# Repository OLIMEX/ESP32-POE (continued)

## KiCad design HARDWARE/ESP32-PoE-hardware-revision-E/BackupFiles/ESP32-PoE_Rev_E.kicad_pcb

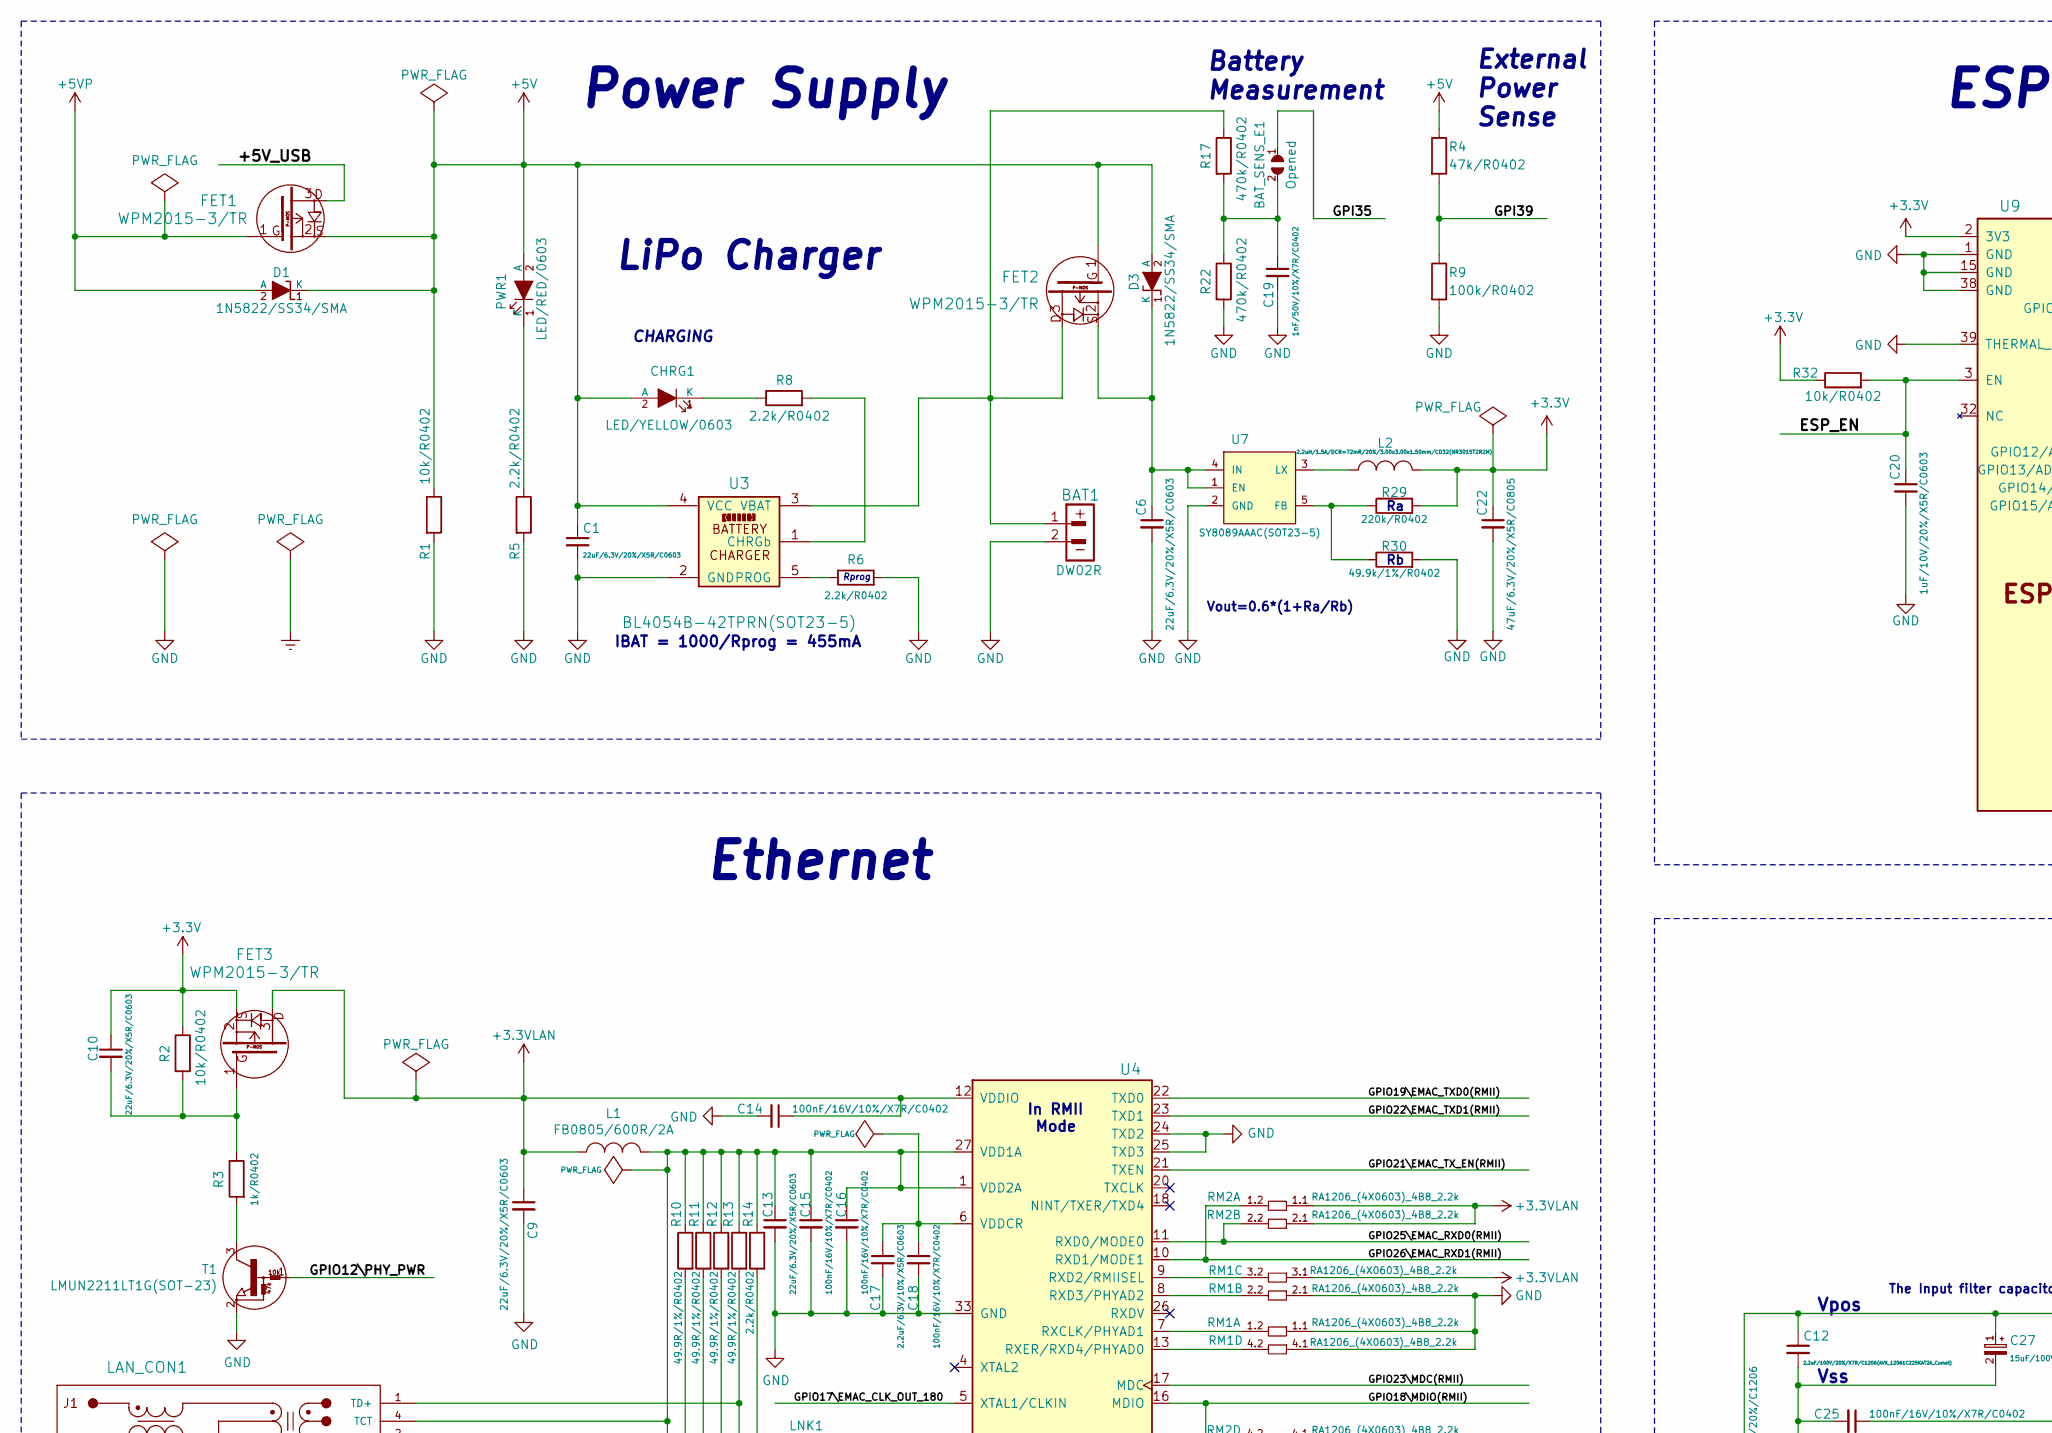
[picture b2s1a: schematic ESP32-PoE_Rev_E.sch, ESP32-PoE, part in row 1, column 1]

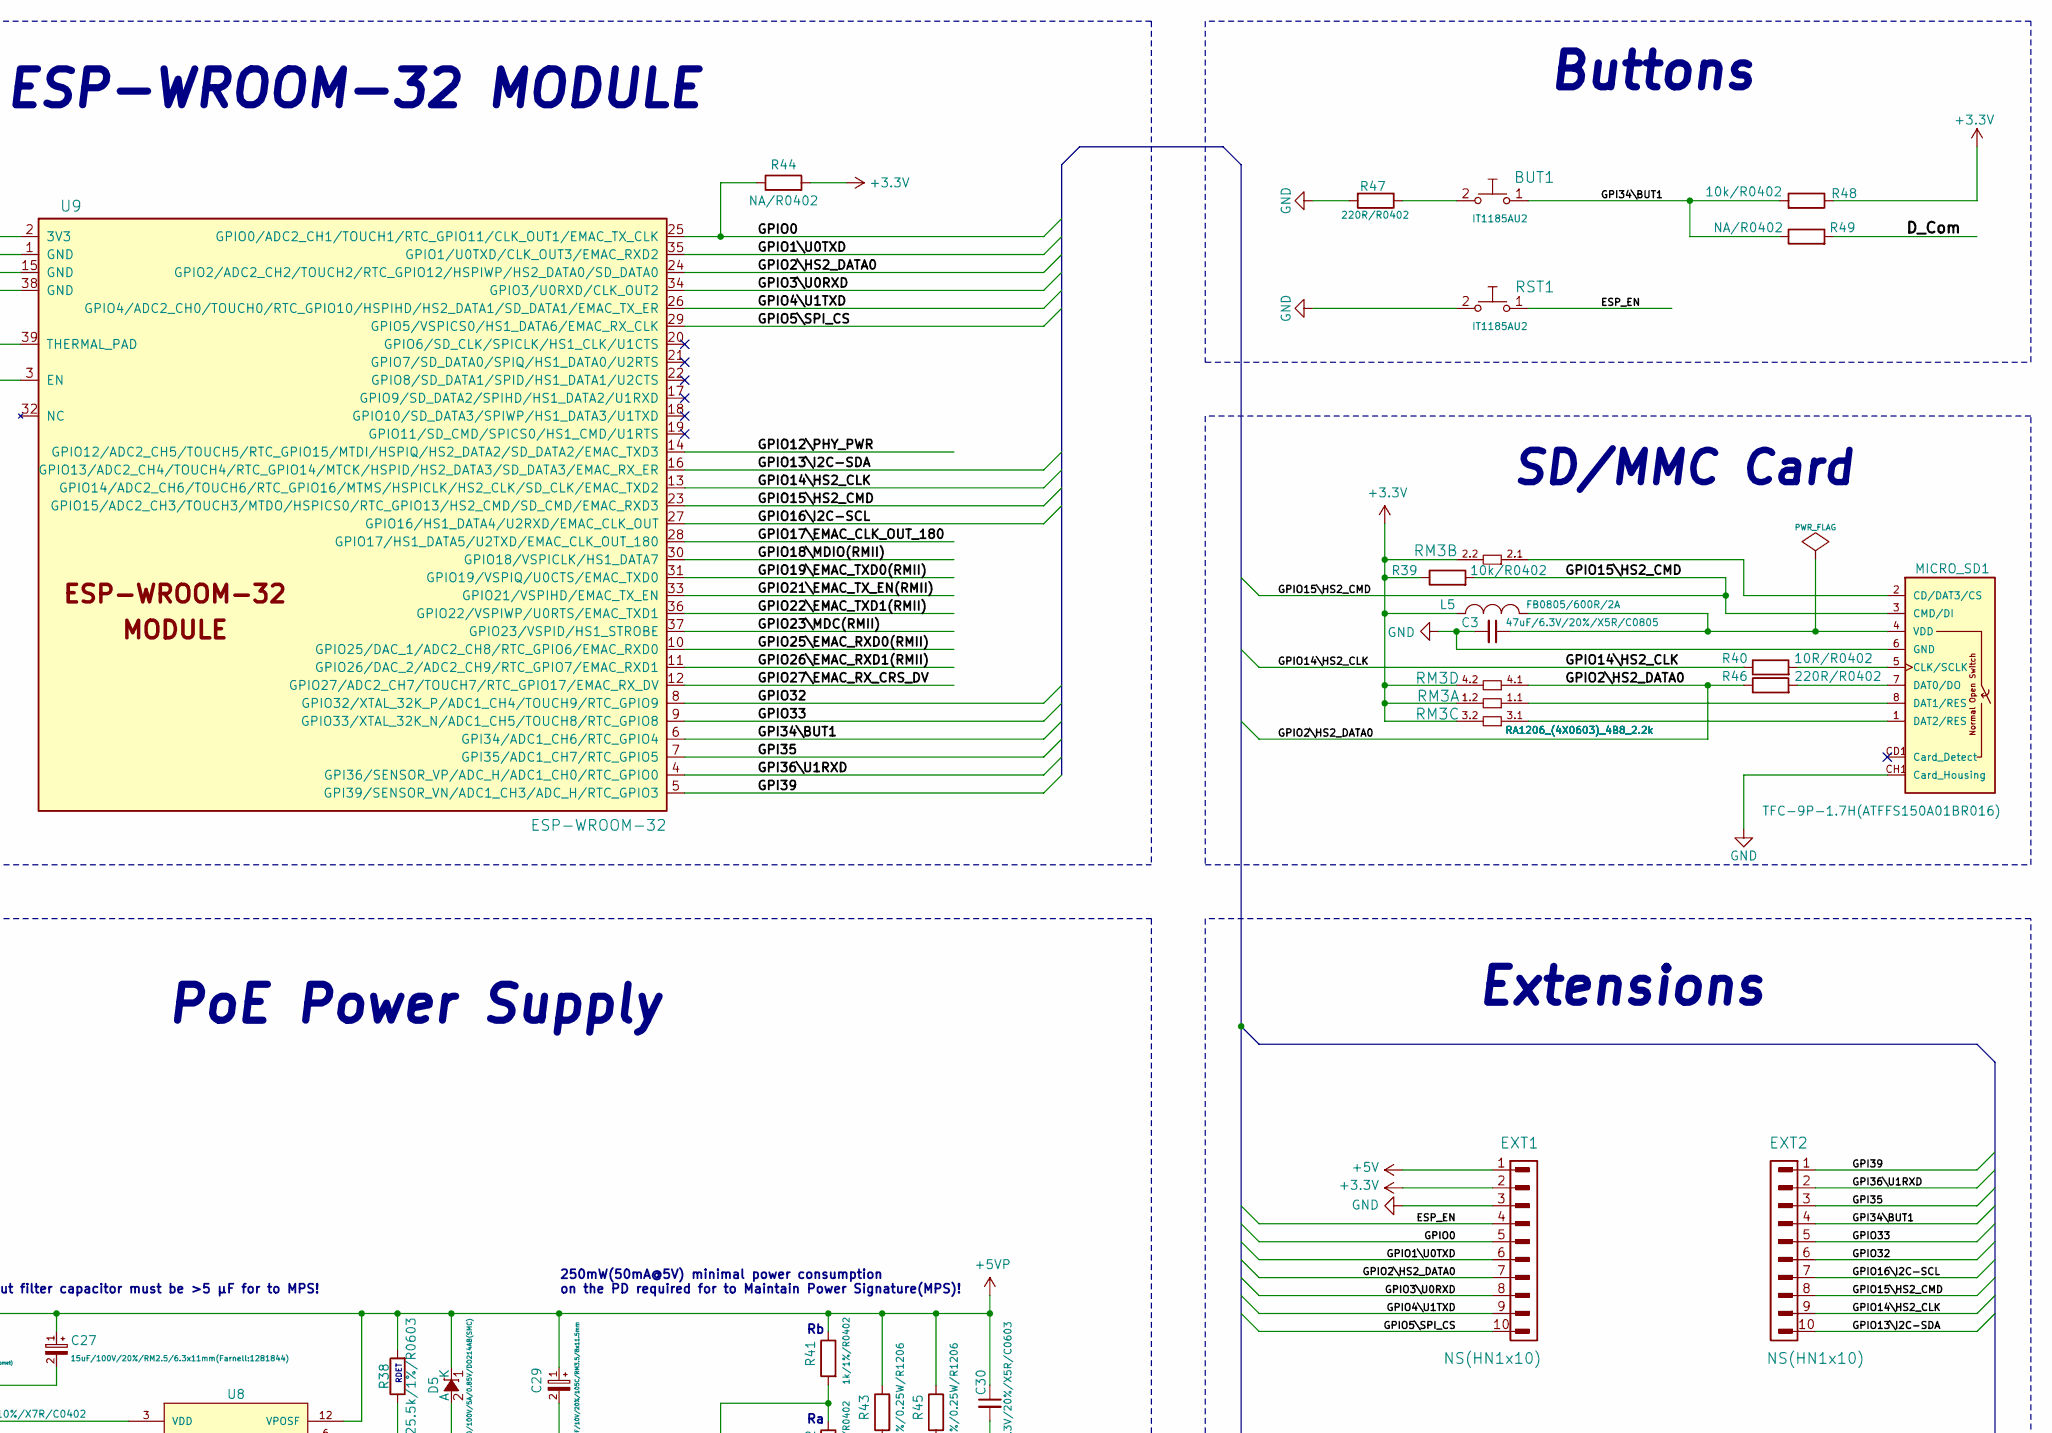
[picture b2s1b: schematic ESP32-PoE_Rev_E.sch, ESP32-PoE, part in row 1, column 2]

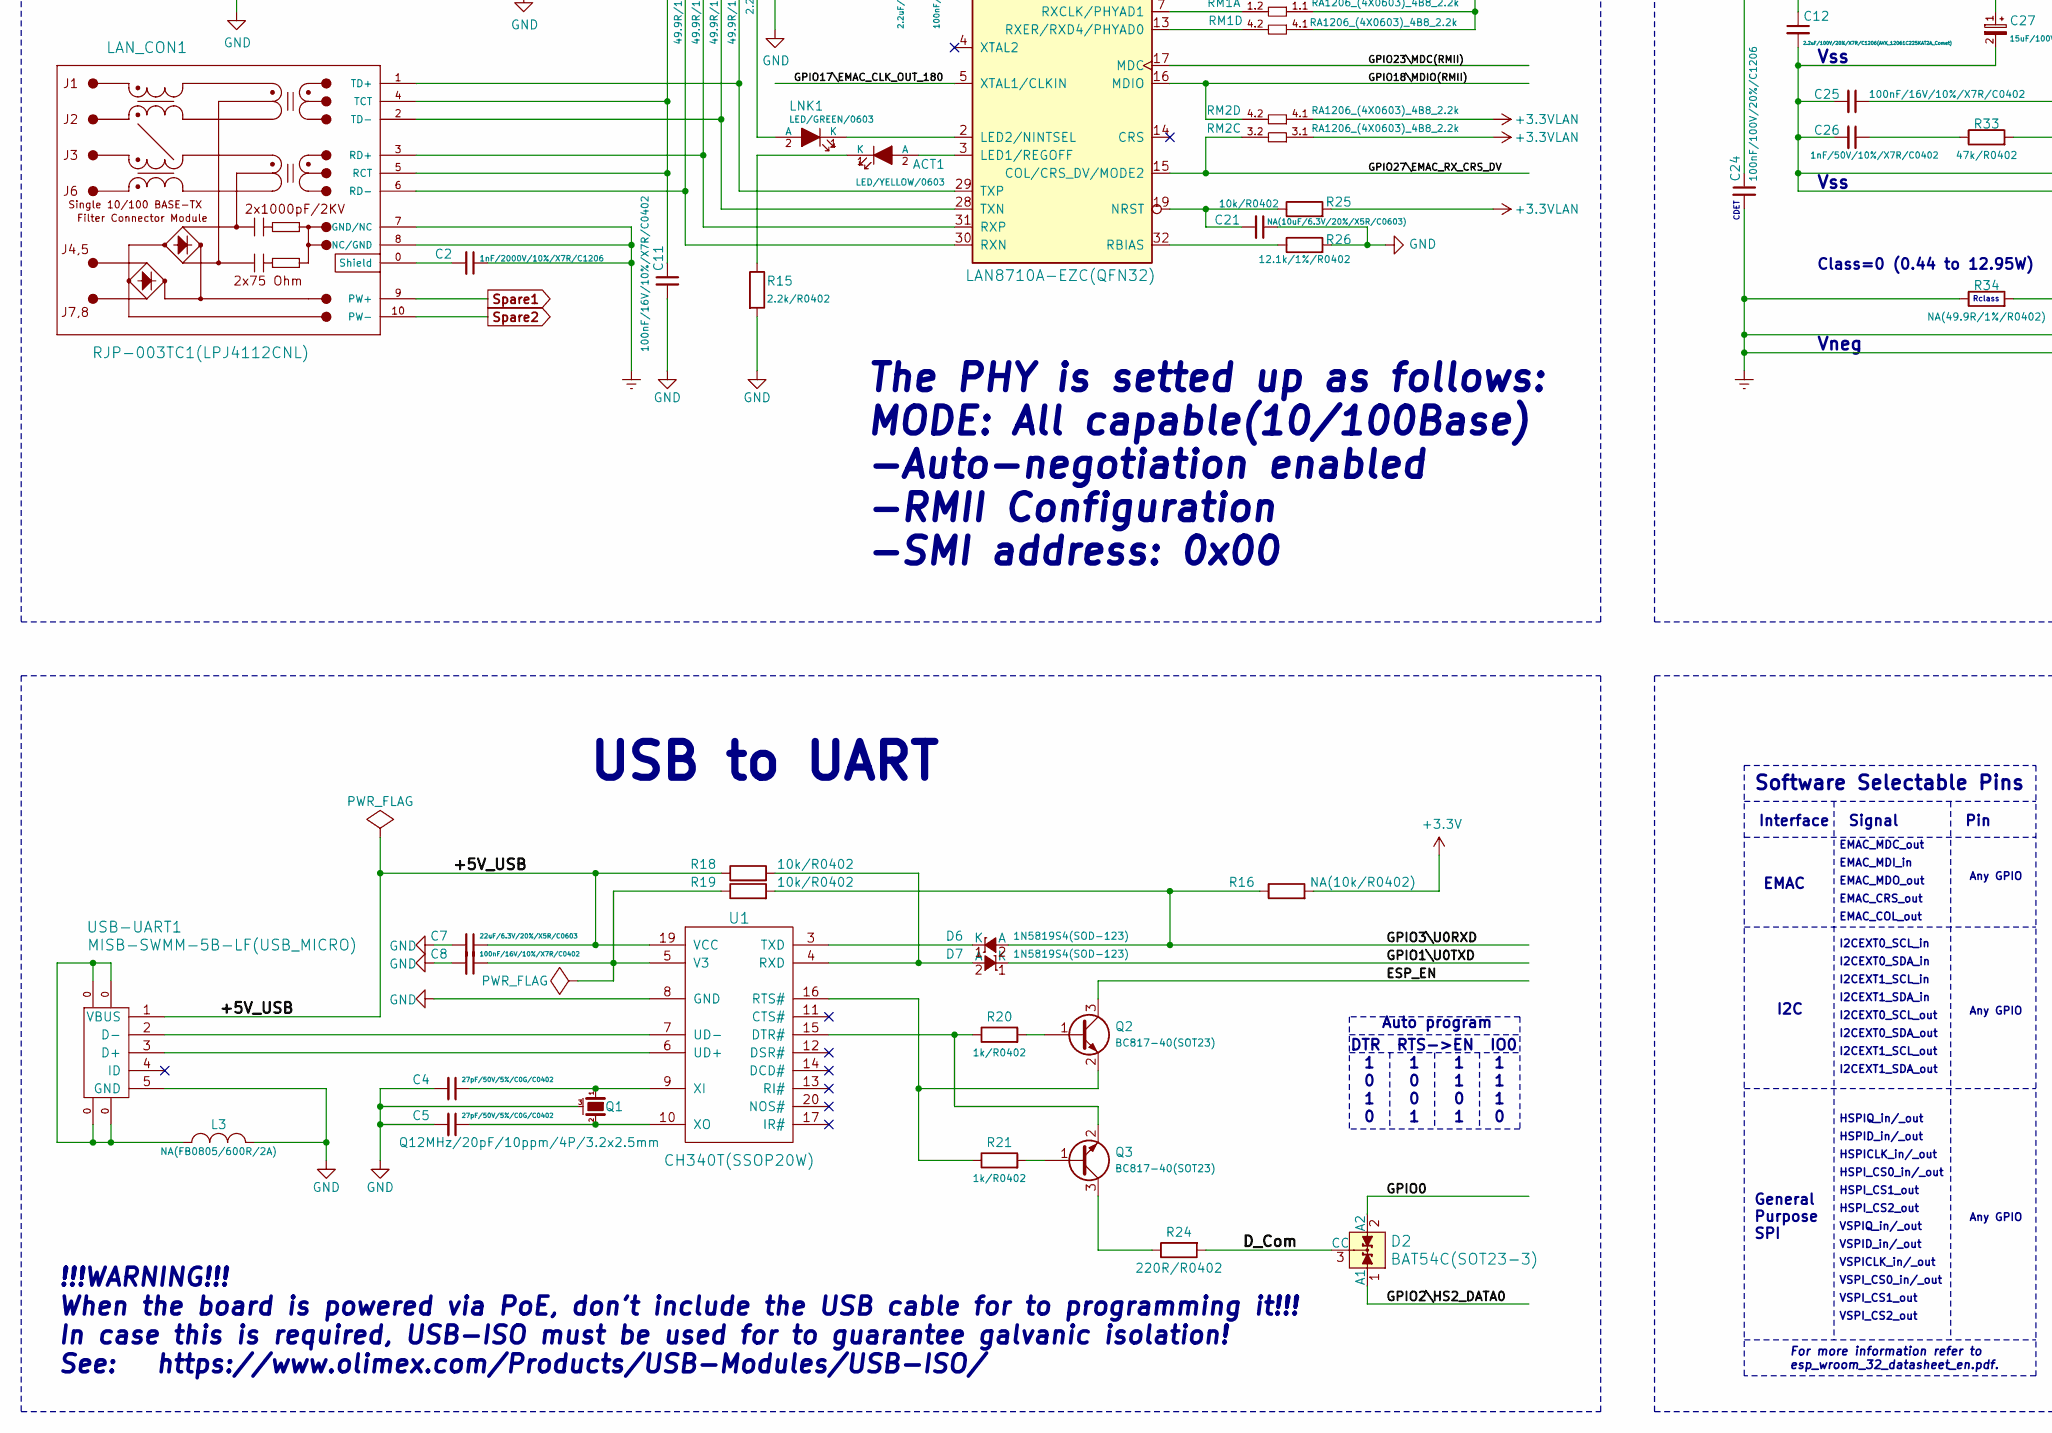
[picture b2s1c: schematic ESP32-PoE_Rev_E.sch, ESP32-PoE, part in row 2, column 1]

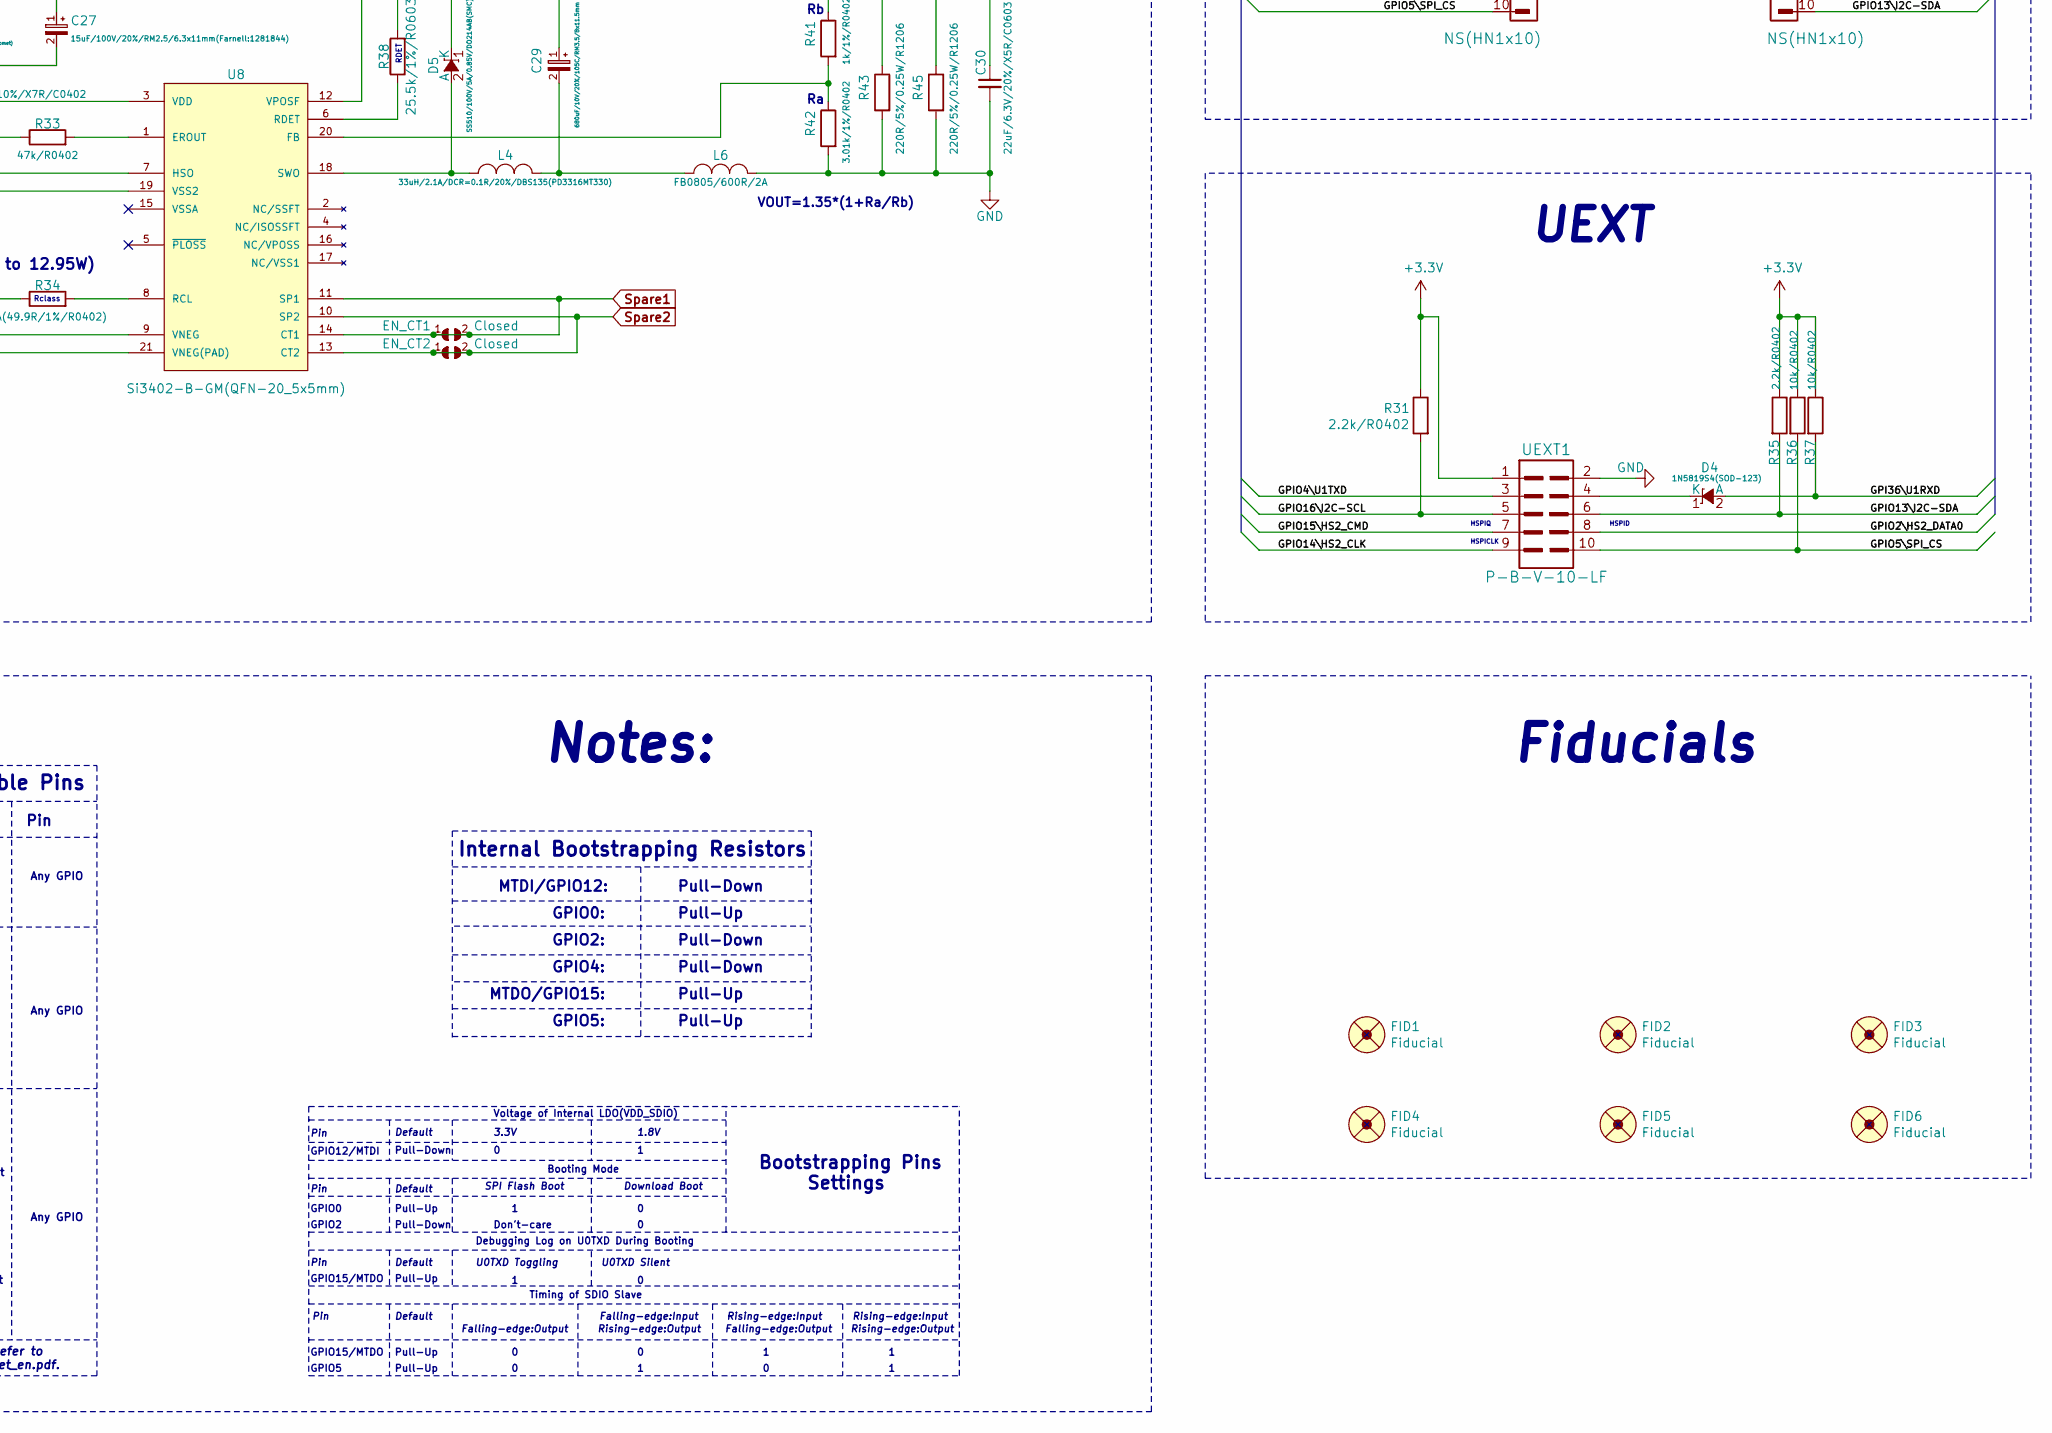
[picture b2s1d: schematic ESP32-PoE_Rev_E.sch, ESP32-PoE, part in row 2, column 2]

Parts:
ACT1: LED/YELLOW/0603; LED_0603_KA
BAT1: DW02R; LIPO_BAT-CON2DW02R
BAT_SENS_E1: Opened; SJ_1_SMALLER
BUT1: IT1185AU2; IT1185AU2_V2
C1, C6, C7, C9, C10, C13, C30: 22uF/6.3V/20%/X5R/C0603; C_0603_5MIL_DWS
C2: 1nF/2000V/10%/X7R/C1206; C_1206_5MIL_DWS_ISO
C3, C22: 47uF/6.3V/20%/X5R/C0805; C_0805_5MIL_DWS
C4, C5: 27pF/50V/5%/C0G/C0402; C_0402_5MIL_DWS
C8, C11, C14, C15, C16, C18, C25: 100nF/16V/10%/X7R/C0402; C_0402_5MIL_DWS
C12: 2.2uF/100V/20%/X7R/C1206(AVX_12061C225KAT2A_Comet); C_1206_5MIL_DWS_ISO
C17: 2.2uF/6.3V/10%/X5R/C0603; C_0603_5MIL_DWS
C19, C26: 1nF/50V/10%/X7R/C0402; C_0402_5MIL_DWS
C20: 1uF/10V/20%/X5R/C0603; C_0603_5MIL_DWS
C21: NA(10uF/6.3V/20%/X5R/C0603); C_0603_5MIL_DWS
C24: 100nF/100V/20%/C1206; C_1206_5MIL_DWS
C27: 15uF/100V/20%/RM2.5/6.3x11mm(Farnell:1281844); CPOL-RM2.5mm_6.3x11mm_SMD
C29: 680uF/10V/20%/105C/RM3.5/8x11.5mm; CPOL-RM3.5mm_8.0x11.5mm_SMD
CHRG1: LED/YELLOW/0603; LED_0603_KA
D1, D3: 1N5822/SS34/SMA; SMA-KA
D2: BAT54C(SOT23-3); SOT23-3
D4, D6, D7: 1N5819S4(SOD-123); SOD-123_1C-2A_KA
D5: SS510/100V/5A/0.85V/DO214AB(SMC); DO214AB(SMC)_1(K)-2(A)
EN_CT1, EN_CT2: Closed; SJ_1_SMALLER
EXT1, EXT2: NS(HN1x10); HN1x10
FET1, FET2, FET3: WPM2015-3/TR; SOT23
FID1, FID2, FID3, FID4, FID5, FID6: Fiducial; Fiducial1x3
L1, L5, L6: FB0805/600R/2A; L_0805_5MIL_DWS
L2: 2.2uH/1.5A/DCR=72mR/20%/3.00x3.00x1.50mm/CD32(NR3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; CD32
L3: NA(FB0805/600R/2A); L_0805_5MIL_DWS
L4: 33uH/2.1A/DCR=0.1R/20%/DBS135(PD3316MT330); DBS135
LAN_CON1: RJP-003TC1(LPJ4112CNL)
LNK1: LED/GREEN/0603; LED_0603_KA
MICRO_SD1: TFC-9P-1.7H(ATFFS150A01BR016); uSD(TFC-9P-1.xH(ATFFS150A01BR016))
PWR1: LED/RED/0603; LED_0603_KA
Q1: Q12MHz/20pF/10ppm/4P/3.2x2.5mm; TSX-3.2x2.5mm_GND(3)
Q2, Q3: BC817-40(SOT23); SOT23
R1, R2, R18, R19, R25, R32, R36, R37, R39, R48: 10k/R0402; R_0402_5MIL_DWS
R3, R20, R21: 1k/R0402; R_0402_5MIL_DWS
R4, R33: 47k/R0402; R_0402_5MIL_DWS
R5, R6, R8, R14, R15, R31, R35: 2.2k/R0402; R_0402_5MIL_DWS
R9: 100k/R0402; R_0402_5MIL_DWS
R10, R11, R12, R13: 49.9R/1%/R0402; R_0402_5MIL_DWS
R16: NA(10k/R0402); R_0402_5MIL_DWS
R17, R22: 470k/R0402; R_0402_5MIL_DWS
R24, R46, R47: 220R/R0402; R_0402_5MIL_DWS
R26: 12.1k/1%/R0402; R_0402_5MIL_DWS
R29: 220k/R0402; R_0402_5MIL_DWS
R30: 49.9k/1%/R0402; R_0402_5MIL_DWS
R34: NA(49.9R/1%/R0402); R_0402_5MIL_DWS
R38: 25.5k/1%/R0603; R_0603_5MIL_DWS
R40: 10R/R0402; R_0402_5MIL_DWS
R41: 1k/1%/R0402; R_0402_5MIL_DWS
R42: 3.01k/1%/R0402; R_0402_5MIL_DWS
R43, R45: 220R/5%/0.25W/R1206; R_1206_5MIL_DWS
R44, R49: NA/R0402; R_0402_5MIL_DWS
RM1, RM2, RM3: RA1206_(4X0603)_4B8_2.2k; R_MATRIX_4
RST1: IT1185AU2; IT1185AU2_V2
T1: LMUN2211LT1G(SOT-23); SOT23
U1: CH340T(SSOP20W); SSOP-20W
U3: BL4054B-42TPRN(SOT23-5); SOT-23-5
U4: LAN8710A-EZC(QFN32); QFN32_EP(33)_5.00x5.00x0.90mm_Pitch_0.50mm
U7: SY8089AAAC(SOT23-5); SOT-23-5
U8: Si3402-B-GM(QFN-20_5x5mm); QFN-20_5x5mm(Si3402-B-GM)
U9: ESP-WROOM-32; ESP-WROOM-32_MODULE
UEXT1: P-B-V-10-LF; GBH-254-SMT-10
USB-UART1: MISB-SWMM-5B-LF(USB_MICRO); USB-MICRO_MISB-SWMM-5B_LF

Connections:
+3.3VLAN: C9.1, C14.1, FET3.3, L1.1, R25.2, RM1.3.1, RM2.1.1, RM2.2.1, RM2.3.1, RM2.4.1, U4.12 (VDDIO)
+3V3: C10.1, C22.1, EXT1.2, FET3.2, L2.2, L5.1, R2.1, R16.2, R29.2, R31.1, R32.1, R35.1, R36.1, R37.1, R39.1, R44.2, R48.1, RM3.1.2, RM3.2.2, RM3.3.2, RM3.4.2, U9.2 (3V3), UEXT1.1
+5V: C1.1, CHRG1.2 (A), D1.1 (K), D3.2 (A), EXT1.1, FET1.2, FET2.1, PWR1.2 (A), R1.1, R4.1, U3.4 (VCC)
+5VP: C12.1, C24.1, C27.1 (+), C29.1 (+), C30.1, D1.2 (A), D5.1 (K), FET1.1, R38.2, R41.1, R43.1, R45.1, U8.12 (VPOSF)
/+5V_USB: C7.1, FET1.3, R18.1, U1.19 (VCC), USB-UART1.1 (VBUS)
/D_Com: D2.3 (CC), R24.2, R49.2
/ESP_EN: C20.1, EXT1.4, Q2.3 (C), R32.2, RST1.1, U9.3 (EN)
/GPI34\BUT1: BUT1.1, EXT2.4, R48.2, R49.1, U9.6 (GPI34/ADC1_CH6/RTC_GPIO4)
/GPI35: BAT_SENS_E1.1, EXT2.3, U9.7 (GPI35/ADC1_CH7/RTC_GPIO5)
/GPI36\U1RXD: D4.2 (A), EXT2.2, R37.2, U9.4 (GPI36/SENSOR_VP/ADC_H/ADC1_CH0/RTC_GPIO0)
/GPI39: EXT2.1, R4.2, R9.1, U9.5 (GPI39/SENSOR_VN/ADC1_CH3/ADC_H/RTC_GPIO3)
/GPIO0: D2.2 (A2), EXT1.5, R44.1, U9.25 (GPIO0/ADC2_CH1/TOUCH1/RTC_GPIO11/CLK_OU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)
/GPIO1\U0TXD: D7.1 (K), EXT1.6, U9.35 (GPIO1/U0TXD/CLK_OUT3/EMAC_RXD2)
/GPIO2\HS2_DATA0: D2.1 (A1), EXT1.7, R46.1, RM3.4.1, U9.24 (GPIO2/ADC2_CH2/TOUCH2/RTC_GPIO12/HSPIWP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), UEXT1.8
/GPIO3\U0RXD: D6.2 (A), EXT1.8, R16.1, R19.2, U9.34 (GPIO3/U0RXD/CLK_OUT2)
/GPIO4\U1TXD: EXT1.9, U9.26 (GPIO4/ADC2_CH0/TOUCH0/RTC_GPIO10/HSPIHD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), UEXT1.3
/GPIO5\SPI_CS: EXT1.10, R36.2, U9.29 (GPIO5/VSPICS0/HS1_DATA6/EMAC_RX_CLK), UEXT1.10
/GPIO12\PHY_PWR: T1.1 (B), U9.14 (GPIO12/ADC2_CH5/TOUCH5/RTC_GPIO15/MTDI/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)
/GPIO13\I2C-SDA: EXT2.10, R35.2, U9.16 (GPIO13/ADC2_CH4/TOUCH4/RTC_GPIO14/MTCK/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), UEXT1.6
/GPIO14\HS2_CLK: EXT2.9, R40.1, U9.13 (GPIO14/ADC2_CH6/TOUCH6/RTC_GPIO16/MTMS/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), UEXT1.9
/GPIO15\HS2_CMD: EXT2.8, MICRO_SD1.3 (CMD/DI), R39.2, U9.23 (GPIO15/ADC2_CH3/TOUCH3/MTDO/HSPICS0/RTC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), UEXT1.7
/GPIO16\I2C-SCL: EXT2.7, R31.2, U9.27 (GPIO16/HS1_DATA4/U2RXD/EMAC_CLK_OUT), UEXT1.5
/GPIO17\EMAC_CLK_OUT_180: U4.5 (XTAL1/CLKIN), U9.28 (GPIO17/HS1_DATA5/U2TXD/EMAC_CLK_OUT_180)
/GPIO18\MDIO(RMII): RM2.4.2, U4.16 (MDIO), U9.30 (GPIO18/VSPICLK/HS1_DATA7)
/GPIO19\EMAC_TXD0(RMII): U4.22 (TXD0), U9.31 (GPIO19/VSPIQ/U0CTS/EMAC_TXD0)
/GPIO21\EMAC_TX_EN(RMII): U4.21 (TXEN), U9.33 (GPIO21/VSPIHD/EMAC_TX_EN)
/GPIO22\EMAC_TXD1(RMII): U4.23 (TXD1), U9.36 (GPIO22/VSPIWP/U0RTS/EMAC_TXD1)
/GPIO23\MDC(RMII): U4.17 (MDC), U9.37 (GPIO23/VSPID/HS1_STROBE)
/GPIO25\EMAC_RXD0(RMII): RM2.2.2, U4.11 (RXD0/MODE0), U9.10 (GPIO25/DAC_1/ADC2_CH8/RTC_GPIO6/EMAC_RX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)
/GPIO26\EMAC_RXD1(RMII): RM2.1.2, U4.10 (RXD1/MODE1), U9.11 (GPIO26/DAC_2/ADC2_CH9/RTC_GPIO7/EMAC_RX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)
/GPIO27\EMAC_RX_CRS_DV: RM2.3.2, U4.15 (COL/CRS_DV/MODE2), U9.12 (GPIO27/ADC2_CH7/TOUCH7/RTC_GPIO17/EMAC_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)
/GPIO32: EXT2.6, U9.8 (GPIO32/XTAL_32K_P/ADC1_CH4/TOUCH9/RTC_G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)
/GPIO33: EXT2.5, U9.9 (GPIO33/XTAL_32K_N/ADC1_CH5/TOUCH8/RTC_G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)
Earth: C2.1, C24.2, LAN_CON1.7 (GND/NC), LAN_CON1.8 (NC/GND), R34.1, U8.9 (VNEG), U8.21 (VNEG(PAD))
GND: BAT1.2, C1.2, C3.2, C4.2, C5.2, C6.2, C7.2, C8.2, C9.2, C11.2, C13.2, C14.2, C15.2, C16.2, C17.2, C18.2, C19.2, C20.2, C21.1, C22.2, C30.2, EXT1.3, L3.2, L6.2, MICRO_SD1.6 (GND), MICRO_SD1.CH1 (Card_Housing), Q1.3 (case), R1.2, R5.2, R6.2, R9.2, R15.2, R22.2, R26.2, R30.2, R42.2, R43.2, R45.2, R47.2, RM1.1.1, RM1.2.1, RM1.4.1, RST1.2, T1.2 (E), U1.8 (GND), U3.2 (GND), U4.24 (TXD2), U4.25 (TXD3), U4.33 (GND), U7.2 (GND), U9.1 (GND), U9.15 (GND), U9.38 (GND), U9.39 (THERMAL_PAD), UEXT1.2, USB-UART1.5 (GND)
unnamed: ACT1.1 (K), R15.1
unnamed: ACT1.2 (A), U4.3 (LED1/REGOFF)
unnamed: BAT1.1, FET2.3, R17.1, U3.3 (VBAT)
unnamed: BAT_SENS_E1.2, C19.1, R17.2, R22.1
unnamed: BUT1.2, R47.1
unnamed: C2.2, LAN_CON1.0 (Shield)
unnamed: C3.1, L5.2, MICRO_SD1.4 (VDD)
unnamed: C4.1, Q1.1, U1.9 (XI)
unnamed: C5.1, Q1.2, U1.10 (XO)
unnamed: C6.1, D3.1 (K), FET2.2, U7.1 (EN), U7.4 (IN)
unnamed: C8.1, R19.1, U1.5 (V3)
unnamed: C10.2, FET3.1, R2.2, R3.1
unnamed: C11.1, C13.1, C15.1, C16.1, L1.2, LAN_CON1.4 (TCT), LAN_CON1.5 (RCT), R10.1, R11.1, R12.1, R13.1, R14.1, U4.1 (VDD2A), U4.27 (VDD1A)
unnamed: C12.2, C25.2, C26.2, C27.2 (-), U8.7 (HSO), U8.19 (VSS2)
unnamed: C17.1, C18.1, U4.6 (VDDCR)
unnamed: C21.2, R25.1, U4.19 (NRST)
unnamed: C25.1, U8.3 (VDD)
unnamed: C26.1, R33.1
unnamed: C29.2 (-), L4.2, L6.1
unnamed: CHRG1.1 (K), R8.1
unnamed: D4.1 (K), UEXT1.4
unnamed: D5.2 (A), L4.1, U8.18 (SWO)
unnamed: D6.1 (K), U1.3 (TXD)
unnamed: D7.2 (A), R18.2, U1.4 (RXD)
unnamed: L2.1, U7.3 (LX)
unnamed: L3.1, USB-UART1.0
unnamed: LAN_CON1.1 (TD+), R13.2, U4.29 (TXP)
unnamed: LAN_CON1.2 (TD-), R12.2, U4.28 (TXN)
unnamed: LAN_CON1.3 (RD+), R11.2, U4.31 (RXP)
unnamed: LAN_CON1.6 (RD-), R10.2, U4.30 (RXN)
unnamed: LNK1.1 (K), U4.2 (LED2/NINTSEL)
unnamed: LNK1.2 (A), R14.2
unnamed: MICRO_SD1.1 (DAT2/RES), RM3.3.1
unnamed: MICRO_SD1.2 (CD/DAT3/CS), RM3.2.1
unnamed: MICRO_SD1.5 (CLK/SCLK), R40.2
unnamed: MICRO_SD1.7 (DAT0/DO), R46.2
unnamed: MICRO_SD1.8 (DAT1/RES), RM3.1.1
unnamed: PWR1.1 (K), R5.1
unnamed: Q2.1 (B), R20.2
unnamed: Q2.2 (E), R21.1, U1.16 (RTS#)
unnamed: Q3.1 (B), R21.2
unnamed: Q3.2 (E), R20.1, U1.15 (DTR#)
unnamed: Q3.3 (C), R24.1
unnamed: R3.2, T1.3 (C)
unnamed: R6.1, U3.5 (PROG)
unnamed: R8.2, U3.1 (CHRGb)
unnamed: R26.1, U4.32 (RBIAS)
unnamed: R29.1, R30.1, U7.5 (FB)
unnamed: R33.2, U8.1 (EROUT)
unnamed: R34.2, U8.8 (RCL)
unnamed: R38.1, U8.6 (RDET)
unnamed: R41.2, R42.1, U8.20 (FB)
unnamed: RM1.1.2, U4.7 (RXCLK/PHYAD1)
unnamed: RM1.2.2, U4.8 (RXD3/PHYAD2)
unnamed: RM1.3.2, U4.9 (RXD2/RMIISEL)
unnamed: RM1.4.2, U4.13 (RXER/RXD4/PHYAD0)
unnamed: U1.6 (UD+), USB-UART1.3 (D+)
unnamed: U1.7 (UD-), USB-UART1.2 (D-)
Spare1: EN_CT1.1, EN_CT1.2, LAN_CON1.9 (PW+), U8.11 (SP1), U8.14 (CT1)
Spare2: EN_CT2.1, EN_CT2.2, LAN_CON1.10 (PW-), U8.10 (SP2), U8.13 (CT2)

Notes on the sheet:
Vout=0.6*(1+Ra/Rb)
Power Supply
Buttons
UEXT
In RMII Mode
Ethernet
ESP-WROOM-32 MODULE
SD/MMC Card
Bootstrapping Pins Settings
Internal Bootstrapping Resistors
MTDI/GPIO12:
Pull-Down
GPIO0:
Pull-Up
GPIO2:
GPIO4:
MTDO/GPIO15:
GPIO5:
Voltage of Internal LDO(VDD_SDIO)
Pin
Default
3.3V
1.8V
Booting Mode
GPIO12/MTDI
GPIO0
GPIO2
SPI Flash Boot
Download Boot
Don't-care
Debugging Log on U0TXD During Booting
U0TXD Toggling
U0TXD Silent
GPIO15/MTDO
Timing of SDIO Slave
For more information refer to esp_wroom_32_datasheet_en.pdf.
Falling-edge:Output
Falling-edge:Input
Rising-edge:Output
Rising-edge:Input

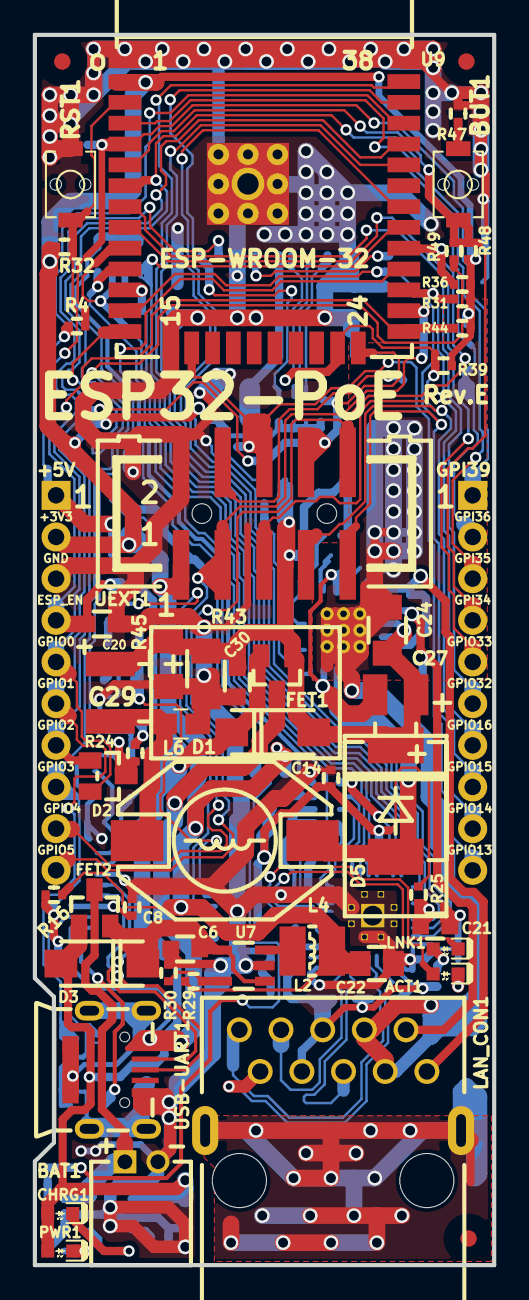
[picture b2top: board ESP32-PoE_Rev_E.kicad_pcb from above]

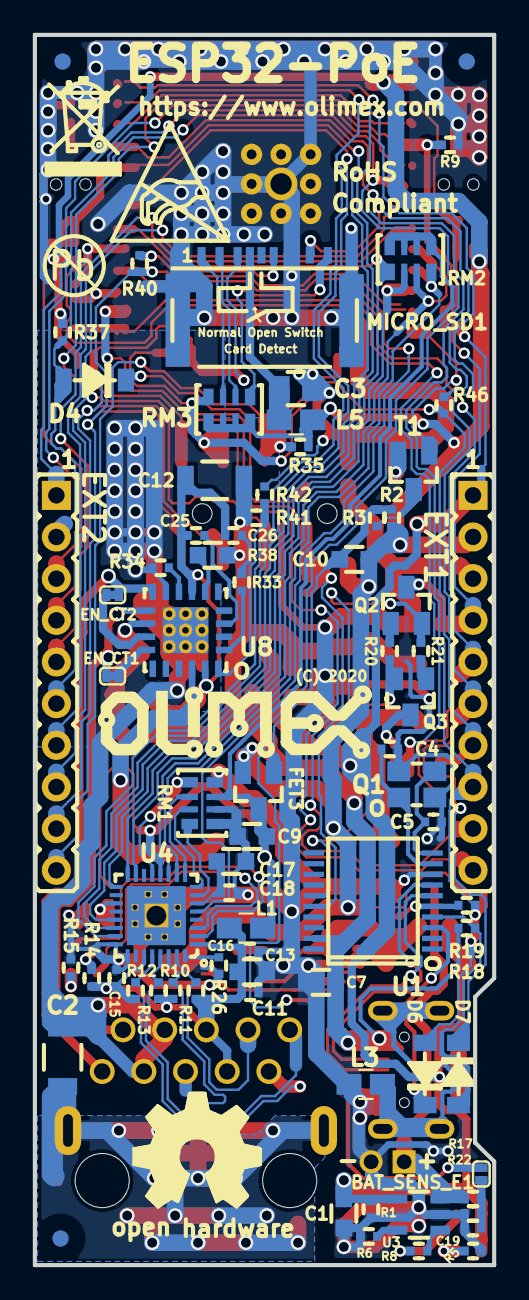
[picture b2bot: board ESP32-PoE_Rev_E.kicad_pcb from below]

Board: 2 copper layers, 28.0 x 75.0 mm, 129 parts (79 on the bottom side), 95 nets.

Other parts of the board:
Logo_OSHW: LOGO_OPENHARDWARE_8x8
Logo_Olimex: OLIMEX_LOGO_TB
Sign_Antistatic: Val**; LOGO_ANTISTATIC_1
Sign_PB-Free: LOGO_PBFREE
Sign_RecycleBin: LOGO_RECYCLEBIN_1

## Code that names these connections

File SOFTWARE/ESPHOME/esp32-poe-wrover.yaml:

esphome:
  name: esp32-poe-wrover
  comment: Olimex ESP32-POE WROVER N4R8 variant with PSRAM and UEXT support

esp32:
  board: esp32dev
  flash_size: 4MB
  framework:
    type: arduino

psram:
  mode: quad
  speed: 80MHz

logger:

# ================= NETWORKING =================

# ---- WiFi (Primary) ----
# Add these entries to secrets.yaml:
# wifi_ssid: "your_wifi_name"
# wifi_password: "your_wifi_password"
wifi:
  ssid: !secret wifi_ssid
  password: !secret wifi_password
  ap:
    ssid: "ESP32-POE-WROVER Fallback"
    password: "fallback123"

captive_portal:

# ---- Ethernet (Alternative to WiFi) ----
# ESPHome cannot use WiFi and Ethernet at the same time.
# To use Ethernet:
#   1. Comment the whole wifi: section above
#   2. Comment captive_portal:
#   3. Uncomment the ethernet: section below
#
# WROVER variants use GPIO0 as Ethernet clock output.
#
#ethernet:
#  type: LAN8720
#  mdc_pin: GPIO23
#  mdio_pin: GPIO18
#  clk:
#    pin: GPIO0
#    mode: CLK_OUT
#  phy_addr: 0
#  power_pin:
#    number: GPIO12
#    ignore_strapping_warning: true

# ================= ONBOARD IO =================

# ---- User Button (BUT1) ----
binary_sensor:
  - platform: gpio
    name: "BUT1 Button"
    pin:
      number: GPIO34
      mode:
        input: true
      inverted: true

# ---- External Power Sense ----
sensor:
  - platform: adc
    pin: GPIO39
    name: "External Power Sense"
    attenuation: 12db
    update_interval: 10s

# ---- Optional Battery Sense ----
# Requires closing the battery sense solder jumper on boards that support it.
#
#  - platform: adc
#    pin: GPIO35
#    name: "Battery Sense"
#    attenuation: 12db
#    update_interval: 10s

# ================= UEXT CONNECTOR =================

# ---- UART on UEXT ----
uart:
  - id: uext_uart
    tx_pin: GPIO4
    rx_pin: GPIO36
    baud_rate: 115200

# ---- I2C Bus on UEXT ----
# WROVER variants use GPIO33 instead of GPIO16 for UEXT SCL.
i2c:
  - id: uext_i2c
    scl: GPIO33
    sda: GPIO13
    scan: true

# ---- SPI Bus on UEXT ----
# UEXT pin 8 MOSI is GPIO2, pin 7 MISO is GPIO15.
# These pins are shared with the microSD interface.
spi:
  - id: uext_spi
    clk_pin: GPIO14
    mosi_pin: GPIO2
    miso_pin: GPIO15

# UEXT SPI chip-select is GPIO5. Add it in the specific SPI device:
#
# cs_pin: GPIO5

# ================= OPTIONAL SD CARD (DISABLED) =================
# To use an SD card, remove the UEXT SPI section above first. SD-card SPI
# uses the same physical pins, but CMD/DATA0 map as MOSI/MISO below.
#
# spi:
#   id: sd_spi
#   clk_pin: GPIO14
#   mosi_pin: GPIO15
#   miso_pin: GPIO2

# ================= CORE SERVICES =================

ota:
  - platform: esphome

api:

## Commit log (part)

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2018-09-06 initial upload
2018-09-07 Update
    Removed redundant text
2018-09-11 Update
    revision B2 update, added change long
2018-11-27 New examples
    All examples
2019-01-02 Update
    Hardware revision C
2019-01-21 Fix typo
2019-02-22 Update
    Added 3D view.
2019-03-11 add ESP32 Nes Emu
2019-04-23 Fixing broken symbols.
    o Adding back missing symbols: Earth and Si3402-B-GM(QFN-20_5x5mm) in
    ESP32-PoE_Rev_C.lib
2019-05-08 Update
    Added second controller (Wii-Nunchuck)
2019-06-13 Added demo
    Added ESP32-PoE iperf demo
2019-07-03 Update
    New example
2019-12-10 Update ethernet example
    Added ethernet example for ESP-IDF v4.0
    Renamed old one to avoid confusions.
2020-01-14 Update
    Latest revision and notes
2020-03-11 Update
    Updated example with the stable 4.0 version of the ESP-IDF following the instructions here:
    https://docs.espressif.com/projects/esp-idf/en/stable/get-started/
2020-06-09 Update
    new revision
2020-10-27 New example
    Ethernet + WIFI Arduino demo
2021-01-07 New example for ethernet
    Espressif example "ethernet\basic" take as a base (ESP-IDF v4.2) and adapted to match the ESP32-POE hardware.
2021-01-08 Update README.md
    Updated README to match the ESP32-PoE hardware and configurations
2021-01-12 Added example
    Example for Azure.
    Combines the original SimpleMQTT example and ETH_LAN8720 so it works with ethernet as well.
2021-04-01 New example
    ESP32 Azure Arduino ETH WIFI example template
2021-08-20 Update
    I2C address changed from 0x76 to 0x77 to match the value defined by the default hardware position of the jumper.
2021-11-05 update
    new reivison
2021-12-17 Update
    Dimensions
2021-12-17 Update
    Added STEP export
2022-02-11 Update
    Updated for IDF 4.4
2022-02-15 Update
    Revision I
2022-04-18 Update
    New eth2ap example
2022-11-15 Update
    Revisions J and K
2022-11-30 New example
    Power sense and battery sense examples
2023-01-04 Update
    New dimensions for revisions J and newer
2023-05-11 Update
    Revision L
2023-05-22 Update
    Added user manual source and PDF export
2023-08-03 New example
    Added WebServer example using ethernet interface (combined 2 Espressif examples).
2023-09-26 Update ESP32_PoE_Ethernet_Arduino.ino
    Additional debug output
2023-09-27 New demo
    MOD-RS485 demo
2023-10-18 Examples update
    Updated ethernet examples with updated macro prefix (from "SYSTEM_" to "ARDUINO_").
2023-11-29 Fix name
2024-01-25 New example
    Added new example for ethernet for the ESP-IDF 5.3
2024-03-03 Added comments for beginners
    (sketch behaviour remains the same)
2024-03-03 Fixed missing LED pinMode assignement
    The LED ont pin 13 does not work without this.
2024-03-03 Added comments + fixed missing LED pin mode assignment
2024-03-03 Additional comments + delay
    Delay is consistent with other script
2024-03-03 Additional comments for beginners
2024-03-05 Update on examples
    Updated Ethernet+SD card example to work with ESP32 package 3.x.x.
    Added an additional comment on the LED pin for the WebServer demo
2025-04-03 Update
    New hardware revision
2025-06-17 New demos
    WIFI + ETH demos, one simple ping, the other with web-server and web-page.
2025-09-03 Update
    New release of the user manual
2025-09-12 Update
    Added info about Ethernet configuration
2025-09-18 Update
    Added notices about LAN initialization and clock
2025-09-19 Update
    New demo for chip info, ram, flash size, etc
2025-11-28 New demo
    MOD-GPS and ESP32-POE/ESP32-POE-ISO demo
2025-12-22 Bluetooth demo
    New demo
2026-02-05 Update
    Web-page demos with visualisation of ESP32 and BME280
2026-02-06 Update
    Added Olimex ESP32-C6 support
2026-05-07 Update
    Added case design for esp32-poe with antenna
2026-05-27 New demo
    ETH->WIFI router NAT demo; proves that WIFI and Ethernet can work simultaneously fine
2026-05-27 fix: V-001 security vulnerability
    Automated security fix generated by OrbisAI Security
2026-05-27 fix: use bounded strlcpy/snprintf in nes_rom.c
    The nes_rom
2026-06-09 Update
    ESPHome configs for ESP32-POE and ESP32-POE-WROVER variants
2026-06-24 Update
    Test with ESPectre
2026-06-24 Added platformio configs
    for esp32-poe and esp32-poe-iso and board variants
2026-06-24 Update
    Added more yamls for all board variants and READMEs for
